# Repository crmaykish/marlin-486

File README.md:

# marlin-486
Homebrew 486 Computer System

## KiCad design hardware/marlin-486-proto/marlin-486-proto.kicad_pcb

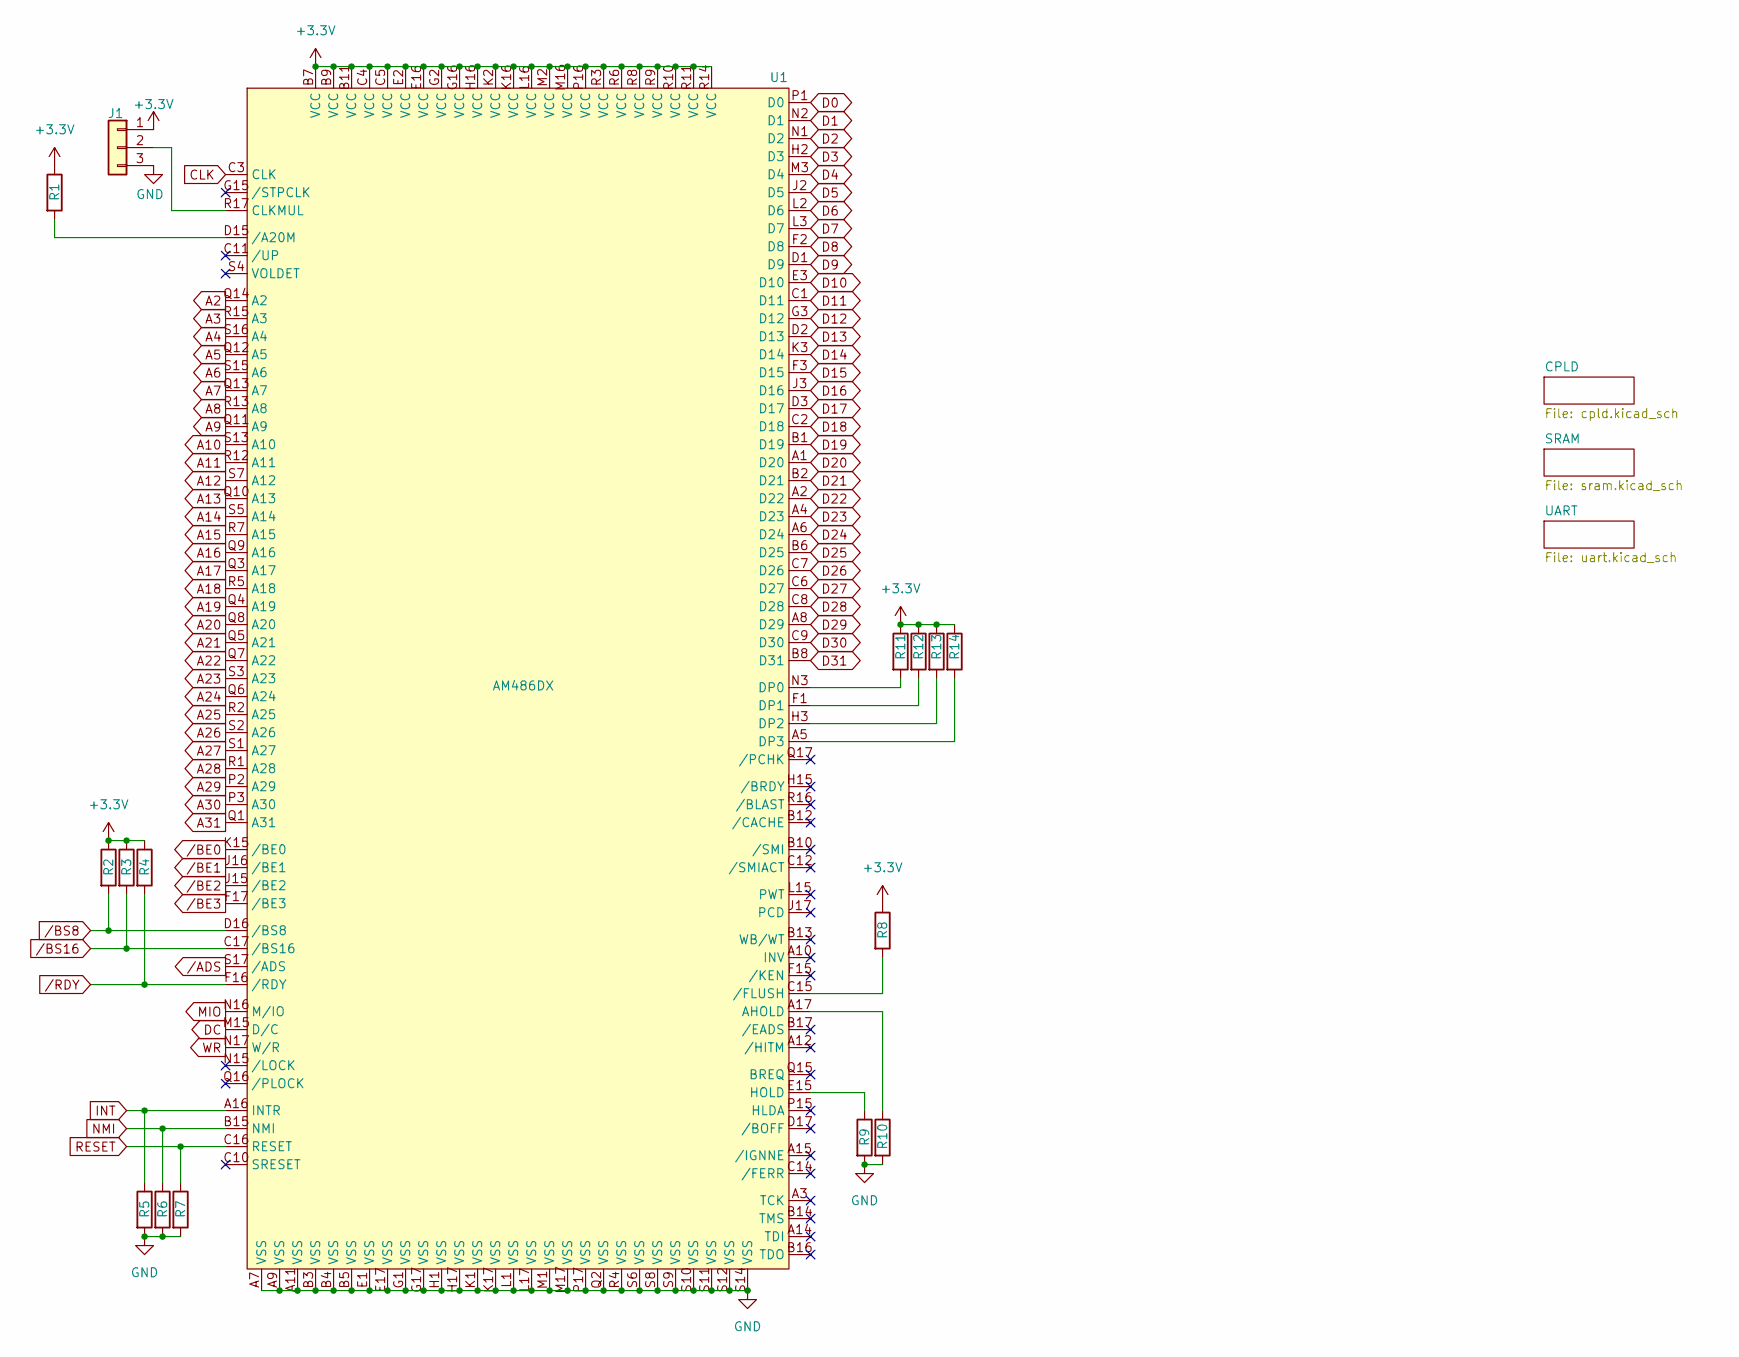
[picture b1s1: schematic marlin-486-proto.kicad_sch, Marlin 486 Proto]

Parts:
J1: Conn_01x03; PinHeader_1x03_P2.54mm_Vertical
R1, R2, R3, R4, R5, R6, R7, R8, R9, R10, R11, R12, R13, R14: 4k7; R_Axial_DIN0207_L6.3mm_D2.5mm_P7.62mm_Horizontal
U1: AM486DX; PGA168

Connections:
+3.3V: J1.1, R1.1, R2.1, R3.1, R4.1, R8.1, R11.1, R12.1, R13.1, R14.1, U1.B7 (VCC), U1.B9 (VCC), U1.B11 (VCC), U1.C4 (VCC), U1.C5 (VCC), U1.E2 (VCC), U1.E16 (VCC), U1.G2 (VCC), U1.G16 (VCC), U1.H16 (VCC), U1.K2 (VCC), U1.K16 (VCC), U1.L16 (VCC), U1.M2 (VCC), U1.M16 (VCC), U1.P16 (VCC), U1.R3 (VCC), U1.R6 (VCC), U1.R8 (VCC), U1.R9 (VCC), U1.R10 (VCC), U1.R11 (VCC), U1.R14 (VCC); also elsewhere on the board
A2: U1.Q14 (A2); also elsewhere on the board
A3: U1.R15 (A3); also elsewhere on the board
A4: U1.S16 (A4); also elsewhere on the board
A5: U1.Q12 (A5); also elsewhere on the board
A6: U1.S15 (A6); also elsewhere on the board
A7: U1.Q13 (A7); also elsewhere on the board
A8: U1.R13 (A8); also elsewhere on the board
A9: U1.Q11 (A9); also elsewhere on the board
A10: U1.S13 (A10); also elsewhere on the board
A11: U1.R12 (A11); also elsewhere on the board
A12: U1.S7 (A12); also elsewhere on the board
A13: U1.Q10 (A13); also elsewhere on the board
A14: U1.S5 (A14); also elsewhere on the board
A15: U1.R7 (A15); also elsewhere on the board
A16: U1.Q9 (A16); also elsewhere on the board
A17: U1.Q3 (A17); also elsewhere on the board
A18: U1.R5 (A18); also elsewhere on the board
A19: U1.Q4 (A19); also elsewhere on the board
A20: U1.Q8 (A20); also elsewhere on the board
A21: U1.Q5 (A21)
A22: U1.Q7 (A22)
A23: U1.S3 (A23)
A24: U1.Q6 (A24)
A25: U1.R2 (A25)
A26: U1.S2 (A26)
A27: U1.S1 (A27)
A28: U1.R1 (A28); also elsewhere on the board
A29: U1.P2 (A29); also elsewhere on the board
A30: U1.P3 (A30); also elsewhere on the board
A31: U1.Q1 (A31); also elsewhere on the board
CLK: U1.C3 (CLK); also elsewhere on the board
D0: U1.P1 (D0); also elsewhere on the board
D1: U1.N2 (D1); also elsewhere on the board
D2: U1.N1 (D2); also elsewhere on the board
D3: U1.H2 (D3); also elsewhere on the board
D4: U1.M3 (D4); also elsewhere on the board
D5: U1.J2 (D5); also elsewhere on the board
D6: U1.L2 (D6); also elsewhere on the board
D7: U1.L3 (D7); also elsewhere on the board
D8: U1.F2 (D8); also elsewhere on the board
D9: U1.D1 (D9); also elsewhere on the board
D10: U1.E3 (D10); also elsewhere on the board
D11: U1.C1 (D11); also elsewhere on the board
D12: U1.G3 (D12); also elsewhere on the board
D13: U1.D2 (D13); also elsewhere on the board
D14: U1.K3 (D14); also elsewhere on the board
D15: U1.F3 (D15); also elsewhere on the board
D16: U1.J3 (D16); also elsewhere on the board
D17: U1.D3 (D17); also elsewhere on the board
D18: U1.C2 (D18); also elsewhere on the board
D19: U1.B1 (D19); also elsewhere on the board
D20: U1.A1 (D20); also elsewhere on the board
D21: U1.B2 (D21); also elsewhere on the board
D22: U1.A2 (D22); also elsewhere on the board
D23: U1.A4 (D23); also elsewhere on the board
D24: U1.A6 (D24); also elsewhere on the board
D25: U1.B6 (D25); also elsewhere on the board
D26: U1.C7 (D26); also elsewhere on the board
D27: U1.C6 (D27); also elsewhere on the board
D28: U1.C8 (D28); also elsewhere on the board
D29: U1.A8 (D29); also elsewhere on the board
D30: U1.C9 (D30); also elsewhere on the board
D31: U1.B8 (D31); also elsewhere on the board
DC: U1.M15 (D/C); also elsewhere on the board
GND: J1.3, R5.2, R6.2, R7.2, R9.2, R10.2, U1.A7 (VSS), U1.A9 (VSS), U1.A11 (VSS), U1.B3 (VSS), U1.B4 (VSS), U1.B5 (VSS), U1.E1 (VSS), U1.E17 (VSS), U1.G1 (VSS), U1.G17 (VSS), U1.H1 (VSS), U1.H17 (VSS), U1.K1 (VSS), U1.K17 (VSS), U1.L1 (VSS), U1.L17 (VSS), U1.M1 (VSS), U1.M17 (VSS), U1.P17 (VSS), U1.Q2 (VSS), U1.R4 (VSS), U1.S6 (VSS), U1.S8 (VSS), U1.S9 (VSS), U1.S10 (VSS), U1.S11 (VSS), U1.S12 (VSS), U1.S14 (VSS); also elsewhere on the board
INT: R5.1, U1.A16 (INTR); also elsewhere on the board
MIO: U1.N16 (M/IO); also elsewhere on the board
NMI: R6.1, U1.B15 (NMI); also elsewhere on the board
unnamed: J1.2, U1.R17 (CLKMUL)
unnamed: R10.1, U1.A17 (AHOLD)
unnamed: R11.2, U1.N3 (DP0)
unnamed: R12.2, U1.F1 (DP1)
unnamed: R13.2, U1.H3 (DP2)
unnamed: R14.2, U1.A5 (DP3)
unnamed: R9.1, U1.E15 (HOLD)
unnamed: R1.2, U1.D15 (/A20M)
unnamed: R8.2, U1.C15 (/FLUSH)
RESET: R7.1, U1.C16 (RESET); also elsewhere on the board
WR: U1.N17 (W/R); also elsewhere on the board
/ADS: U1.S17 (/ADS); also elsewhere on the board
/BE0: U1.K15 (/BE0); also elsewhere on the board
/BE1: U1.J16 (/BE1); also elsewhere on the board
/BE2: U1.J15 (/BE2); also elsewhere on the board
/BE3: U1.F17 (/BE3); also elsewhere on the board
/BS8: R2.2, U1.D16 (/BS8); also elsewhere on the board
/BS16: R3.2, U1.C17 (/BS16); also elsewhere on the board
/RDY: R4.2, U1.F16 (/RDY); also elsewhere on the board

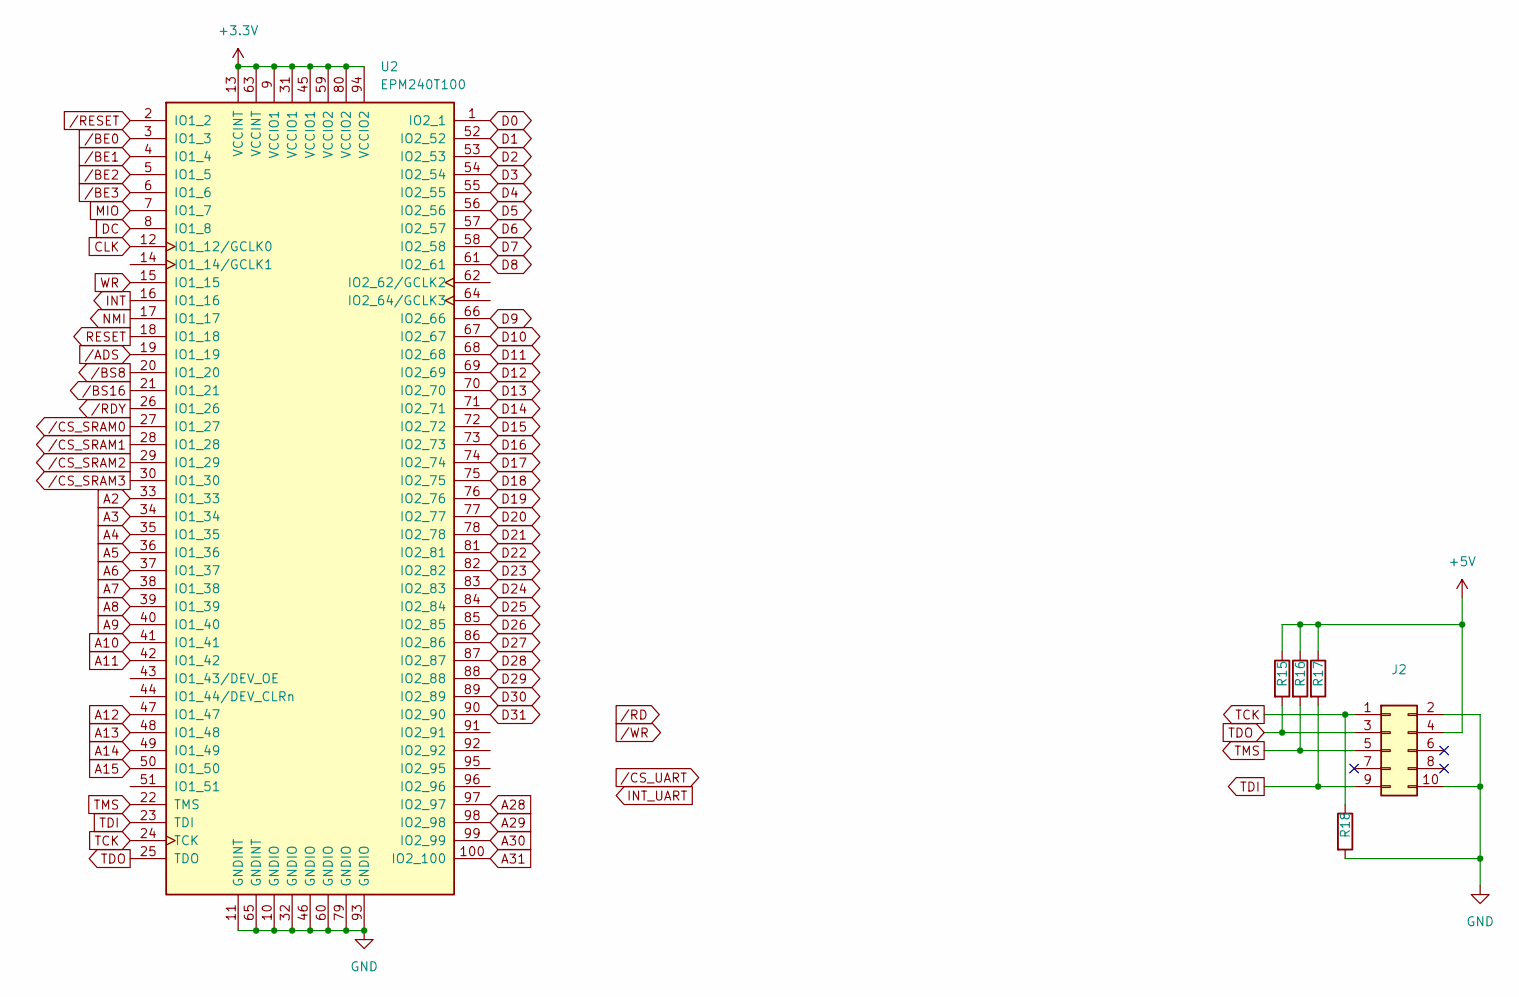
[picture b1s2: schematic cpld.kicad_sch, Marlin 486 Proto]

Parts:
J2: Conn_02x05_Odd_Even; IDC-Header_2x05_P2.54mm_Vertical
R15, R16, R17, R18: 4k7; R_Axial_DIN0207_L6.3mm_D2.5mm_P7.62mm_Horizontal
U2: EPM240T100; LQFP-100_14x14mm_P0.5mm

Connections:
+3.3V: U2.9 (VCCIO1), U2.13 (VCCINT), U2.31 (VCCIO1), U2.45 (VCCIO1), U2.59 (VCCIO2), U2.63 (VCCINT), U2.80 (VCCIO2), U2.94 (VCCIO2); also elsewhere on the board
+5V: J2.4, R15.1, R16.1, R17.1
A2: U2.33 (IO1_33); also elsewhere on the board
A3: U2.34 (IO1_34); also elsewhere on the board
A4: U2.35 (IO1_35); also elsewhere on the board
A5: U2.36 (IO1_36); also elsewhere on the board
A6: U2.37 (IO1_37); also elsewhere on the board
A7: U2.38 (IO1_38); also elsewhere on the board
A8: U2.39 (IO1_39); also elsewhere on the board
A9: U2.40 (IO1_40); also elsewhere on the board
A10: U2.41 (IO1_41); also elsewhere on the board
A11: U2.42 (IO1_42); also elsewhere on the board
A12: U2.47 (IO1_47); also elsewhere on the board
A13: U2.48 (IO1_48); also elsewhere on the board
A14: U2.49 (IO1_49); also elsewhere on the board
A15: U2.50 (IO1_50); also elsewhere on the board
A28: U2.97 (IO2_97); also elsewhere on the board
A29: U2.98 (IO2_98); also elsewhere on the board
A30: U2.99 (IO2_99); also elsewhere on the board
A31: U2.100 (IO2_100); also elsewhere on the board
CLK: U2.12 (IO1_12/GCLK0); also elsewhere on the board
D0: U2.1 (IO2_1); also elsewhere on the board
D1: U2.52 (IO2_52); also elsewhere on the board
D2: U2.53 (IO2_53); also elsewhere on the board
D3: U2.54 (IO2_54); also elsewhere on the board
D4: U2.55 (IO2_55); also elsewhere on the board
D5: U2.56 (IO2_56); also elsewhere on the board
D6: U2.57 (IO2_57); also elsewhere on the board
D7: U2.58 (IO2_58); also elsewhere on the board
D8: U2.61 (IO2_61); also elsewhere on the board
D9: U2.66 (IO2_66); also elsewhere on the board
D10: U2.67 (IO2_67); also elsewhere on the board
D11: U2.68 (IO2_68); also elsewhere on the board
D12: U2.69 (IO2_69); also elsewhere on the board
D13: U2.70 (IO2_70); also elsewhere on the board
D14: U2.71 (IO2_71); also elsewhere on the board
D15: U2.72 (IO2_72); also elsewhere on the board
D16: U2.73 (IO2_73); also elsewhere on the board
D17: U2.74 (IO2_74); also elsewhere on the board
D18: U2.75 (IO2_75); also elsewhere on the board
D19: U2.76 (IO2_76); also elsewhere on the board
D20: U2.77 (IO2_77); also elsewhere on the board
D21: U2.78 (IO2_78); also elsewhere on the board
D22: U2.81 (IO2_81); also elsewhere on the board
D23: U2.82 (IO2_82); also elsewhere on the board
D24: U2.83 (IO2_83); also elsewhere on the board
D25: U2.84 (IO2_84); also elsewhere on the board
D26: U2.85 (IO2_85); also elsewhere on the board
D27: U2.86 (IO2_86); also elsewhere on the board
D28: U2.87 (IO2_87); also elsewhere on the board
D29: U2.88 (IO2_88); also elsewhere on the board
D30: U2.89 (IO2_89); also elsewhere on the board
D31: U2.90 (IO2_90); also elsewhere on the board
DC: U2.8 (IO1_8); also elsewhere on the board
GND: J2.2, J2.10, R18.2, U2.10 (GNDIO), U2.11 (GNDINT), U2.32 (GNDIO), U2.46 (GNDIO), U2.60 (GNDIO), U2.65 (GNDINT), U2.79 (GNDIO), U2.93 (GNDIO); also elsewhere on the board
INT: U2.16 (IO1_16); also elsewhere on the board
MIO: U2.7 (IO1_7); also elsewhere on the board
NMI: U2.17 (IO1_17); also elsewhere on the board
RESET: U2.18 (IO1_18); also elsewhere on the board
TCK: J2.1, R18.1, U2.24 (TCK)
TDI: J2.9, R17.2, U2.23 (TDI)
TDO: J2.3, R15.2, U2.25 (TDO)
TMS: J2.5, R16.2, U2.22 (TMS)
WR: U2.15 (IO1_15); also elsewhere on the board
/ADS: U2.19 (IO1_19); also elsewhere on the board
/BE0: U2.3 (IO1_3); also elsewhere on the board
/BE1: U2.4 (IO1_4); also elsewhere on the board
/BE2: U2.5 (IO1_5); also elsewhere on the board
/BE3: U2.6 (IO1_6); also elsewhere on the board
/BS8: U2.20 (IO1_20); also elsewhere on the board
/BS16: U2.21 (IO1_21); also elsewhere on the board
/CS_SRAM0: U2.27 (IO1_27); also elsewhere on the board
/CS_SRAM1: U2.28 (IO1_28); also elsewhere on the board
/CS_SRAM2: U2.29 (IO1_29); also elsewhere on the board
/CS_SRAM3: U2.30 (IO1_30); also elsewhere on the board
/RDY: U2.26 (IO1_26); also elsewhere on the board
/RESET: U2.2 (IO1_2)

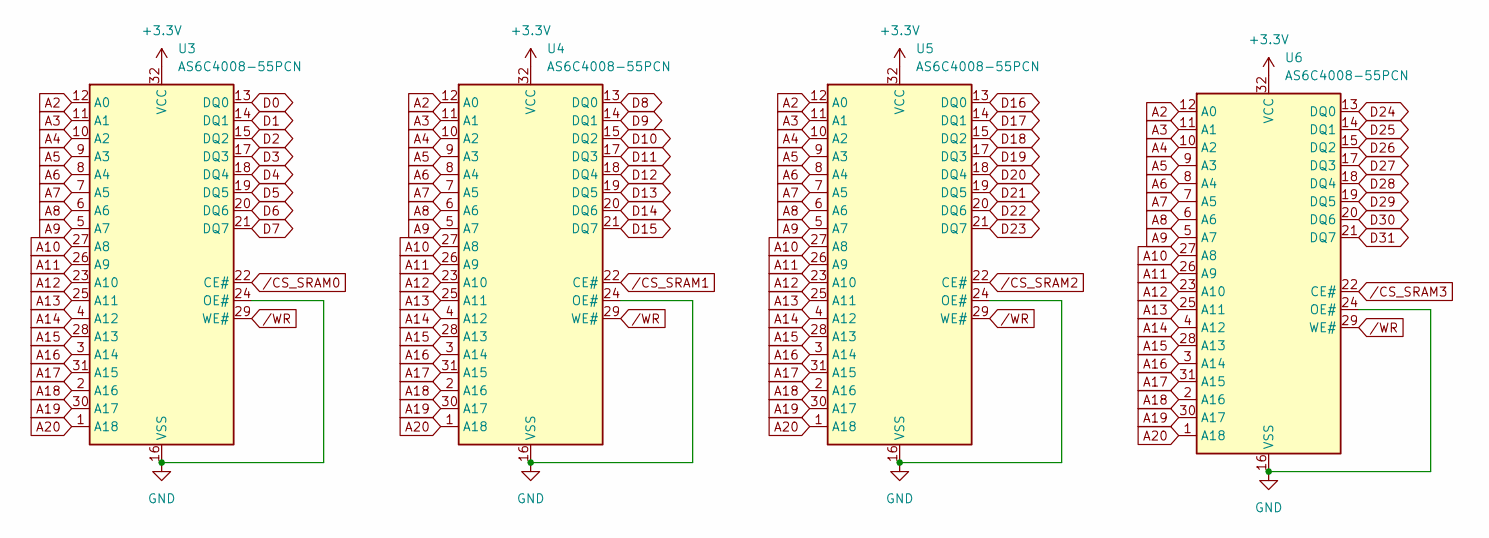
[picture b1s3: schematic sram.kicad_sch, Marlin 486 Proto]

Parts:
U3, U4, U5, U6: AS6C4008-55PCN; DIP-32_W15.24mm_Socket

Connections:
+3.3V: U3.32 (VCC), U4.32 (VCC), U5.32 (VCC), U6.32 (VCC); also elsewhere on the board
A2: U3.12 (A0), U4.12 (A0), U5.12 (A0), U6.12 (A0); also elsewhere on the board
A3: U3.11 (A1), U4.11 (A1), U5.11 (A1), U6.11 (A1); also elsewhere on the board
A4: U3.10 (A2), U4.10 (A2), U5.10 (A2), U6.10 (A2); also elsewhere on the board
A5: U3.9 (A3), U4.9 (A3), U5.9 (A3), U6.9 (A3); also elsewhere on the board
A6: U3.8 (A4), U4.8 (A4), U5.8 (A4), U6.8 (A4); also elsewhere on the board
A7: U3.7 (A5), U4.7 (A5), U5.7 (A5), U6.7 (A5); also elsewhere on the board
A8: U3.6 (A6), U4.6 (A6), U5.6 (A6), U6.6 (A6); also elsewhere on the board
A9: U3.5 (A7), U4.5 (A7), U5.5 (A7), U6.5 (A7); also elsewhere on the board
A10: U3.27 (A8), U4.27 (A8), U5.27 (A8), U6.27 (A8); also elsewhere on the board
A11: U3.26 (A9), U4.26 (A9), U5.26 (A9), U6.26 (A9); also elsewhere on the board
A12: U3.23 (A10), U4.23 (A10), U5.23 (A10), U6.23 (A10); also elsewhere on the board
A13: U3.25 (A11), U4.25 (A11), U5.25 (A11), U6.25 (A11); also elsewhere on the board
A14: U3.4 (A12), U4.4 (A12), U5.4 (A12), U6.4 (A12); also elsewhere on the board
A15: U3.28 (A13), U4.28 (A13), U5.28 (A13), U6.28 (A13); also elsewhere on the board
A16: U3.3 (A14), U4.3 (A14), U5.3 (A14), U6.3 (A14); also elsewhere on the board
A17: U3.31 (A15), U4.31 (A15), U5.31 (A15), U6.31 (A15); also elsewhere on the board
A18: U3.2 (A16), U4.2 (A16), U5.2 (A16), U6.2 (A16); also elsewhere on the board
A19: U3.30 (A17), U4.30 (A17), U5.30 (A17), U6.30 (A17); also elsewhere on the board
A20: U3.1 (A18), U4.1 (A18), U5.1 (A18), U6.1 (A18); also elsewhere on the board
D0: U3.13 (DQ0); also elsewhere on the board
D1: U3.14 (DQ1); also elsewhere on the board
D2: U3.15 (DQ2); also elsewhere on the board
D3: U3.17 (DQ3); also elsewhere on the board
D4: U3.18 (DQ4); also elsewhere on the board
D5: U3.19 (DQ5); also elsewhere on the board
D6: U3.20 (DQ6); also elsewhere on the board
D7: U3.21 (DQ7); also elsewhere on the board
D8: U4.13 (DQ0); also elsewhere on the board
D9: U4.14 (DQ1); also elsewhere on the board
D10: U4.15 (DQ2); also elsewhere on the board
D11: U4.17 (DQ3); also elsewhere on the board
D12: U4.18 (DQ4); also elsewhere on the board
D13: U4.19 (DQ5); also elsewhere on the board
D14: U4.20 (DQ6); also elsewhere on the board
D15: U4.21 (DQ7); also elsewhere on the board
D16: U5.13 (DQ0); also elsewhere on the board
D17: U5.14 (DQ1); also elsewhere on the board
D18: U5.15 (DQ2); also elsewhere on the board
D19: U5.17 (DQ3); also elsewhere on the board
D20: U5.18 (DQ4); also elsewhere on the board
D21: U5.19 (DQ5); also elsewhere on the board
D22: U5.20 (DQ6); also elsewhere on the board
D23: U5.21 (DQ7); also elsewhere on the board
D24: U6.13 (DQ0); also elsewhere on the board
D25: U6.14 (DQ1); also elsewhere on the board
D26: U6.15 (DQ2); also elsewhere on the board
D27: U6.17 (DQ3); also elsewhere on the board
D28: U6.18 (DQ4); also elsewhere on the board
D29: U6.19 (DQ5); also elsewhere on the board
D30: U6.20 (DQ6); also elsewhere on the board
D31: U6.21 (DQ7); also elsewhere on the board
GND: U3.16 (VSS), U3.24 (OE#), U4.16 (VSS), U4.24 (OE#), U5.16 (VSS), U5.24 (OE#), U6.16 (VSS), U6.24 (OE#); also elsewhere on the board
/CS_SRAM0: U3.22 (CE#); also elsewhere on the board
/CS_SRAM1: U4.22 (CE#); also elsewhere on the board
/CS_SRAM2: U5.22 (CE#); also elsewhere on the board
/CS_SRAM3: U6.22 (CE#); also elsewhere on the board
/WR: U3.29 (WE#), U4.29 (WE#), U5.29 (WE#), U6.29 (WE#); also elsewhere on the board

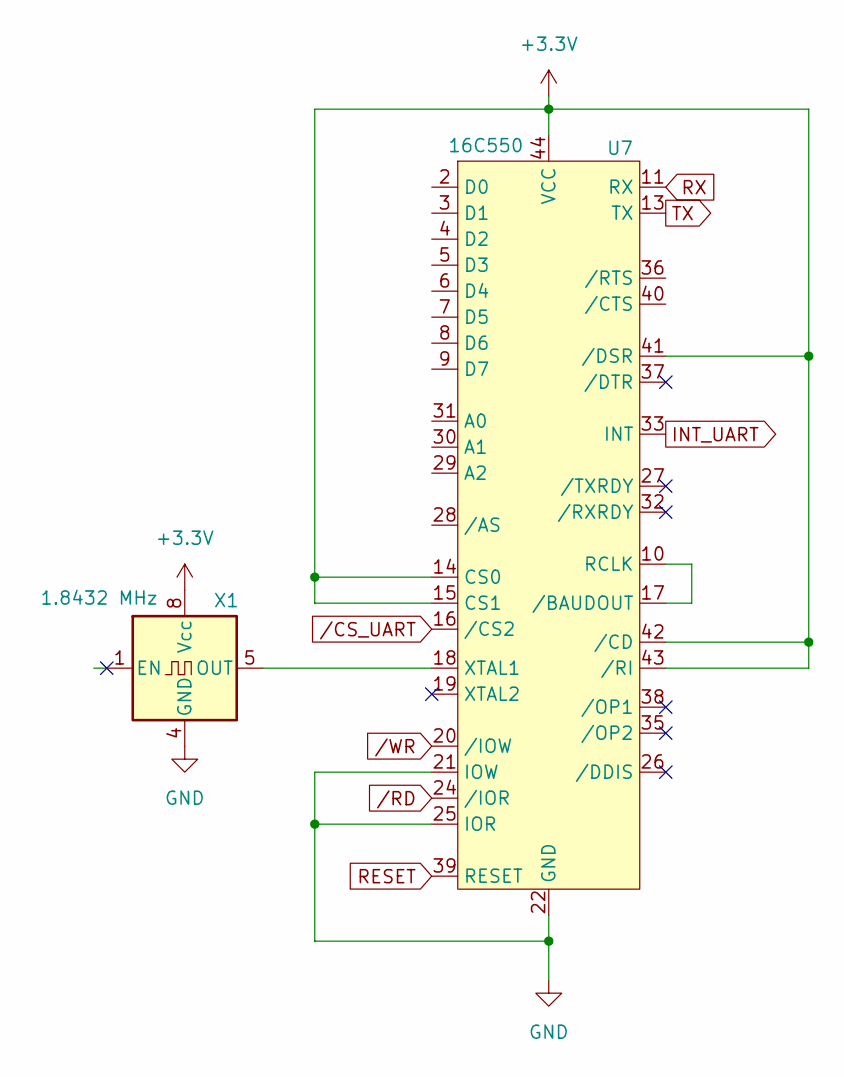
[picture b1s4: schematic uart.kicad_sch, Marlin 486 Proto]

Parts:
U7: 16C550; PLCC-44_THT-Socket
X1: 1.8432 MHz; Oscillator_DIP-8

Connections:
+3.3V: U7.14 (CS0), U7.15 (CS1), U7.41 (/DSR), U7.42 (/CD), U7.43 (/RI), U7.44 (VCC), X1.8 (Vcc); also elsewhere on the board
GND: U7.21 (IOW), U7.22 (GND), U7.25 (IOR), X1.4 (GND); also elsewhere on the board
INT_UART: U7.33 (INT)
unnamed: U7.10 (RCLK), U7.17 (/BAUDOUT)
unnamed: U7.18 (XTAL1), X1.5 (OUT)
RESET: U7.39 (RESET); also elsewhere on the board
RX: U7.11 (RX)
TX: U7.13 (TX)
/CS_UART: U7.16 (/CS2)
/RD: U7.24 (/IOR)
/WR: U7.20 (/IOW); also elsewhere on the board

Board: 2 copper layers, 28 parts (1 on the bottom side), 93 nets, no tracks yet.

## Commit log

2024-10-30 Created Am486DX KiCAD symbol
2024-10-31 Fix pin types on Am486DX symbol
2024-11-11 Minimal CPU wiring
2024-11-14 Add 16C550 symbol
2025-02-09 Add bus sizing charts from datasheet
